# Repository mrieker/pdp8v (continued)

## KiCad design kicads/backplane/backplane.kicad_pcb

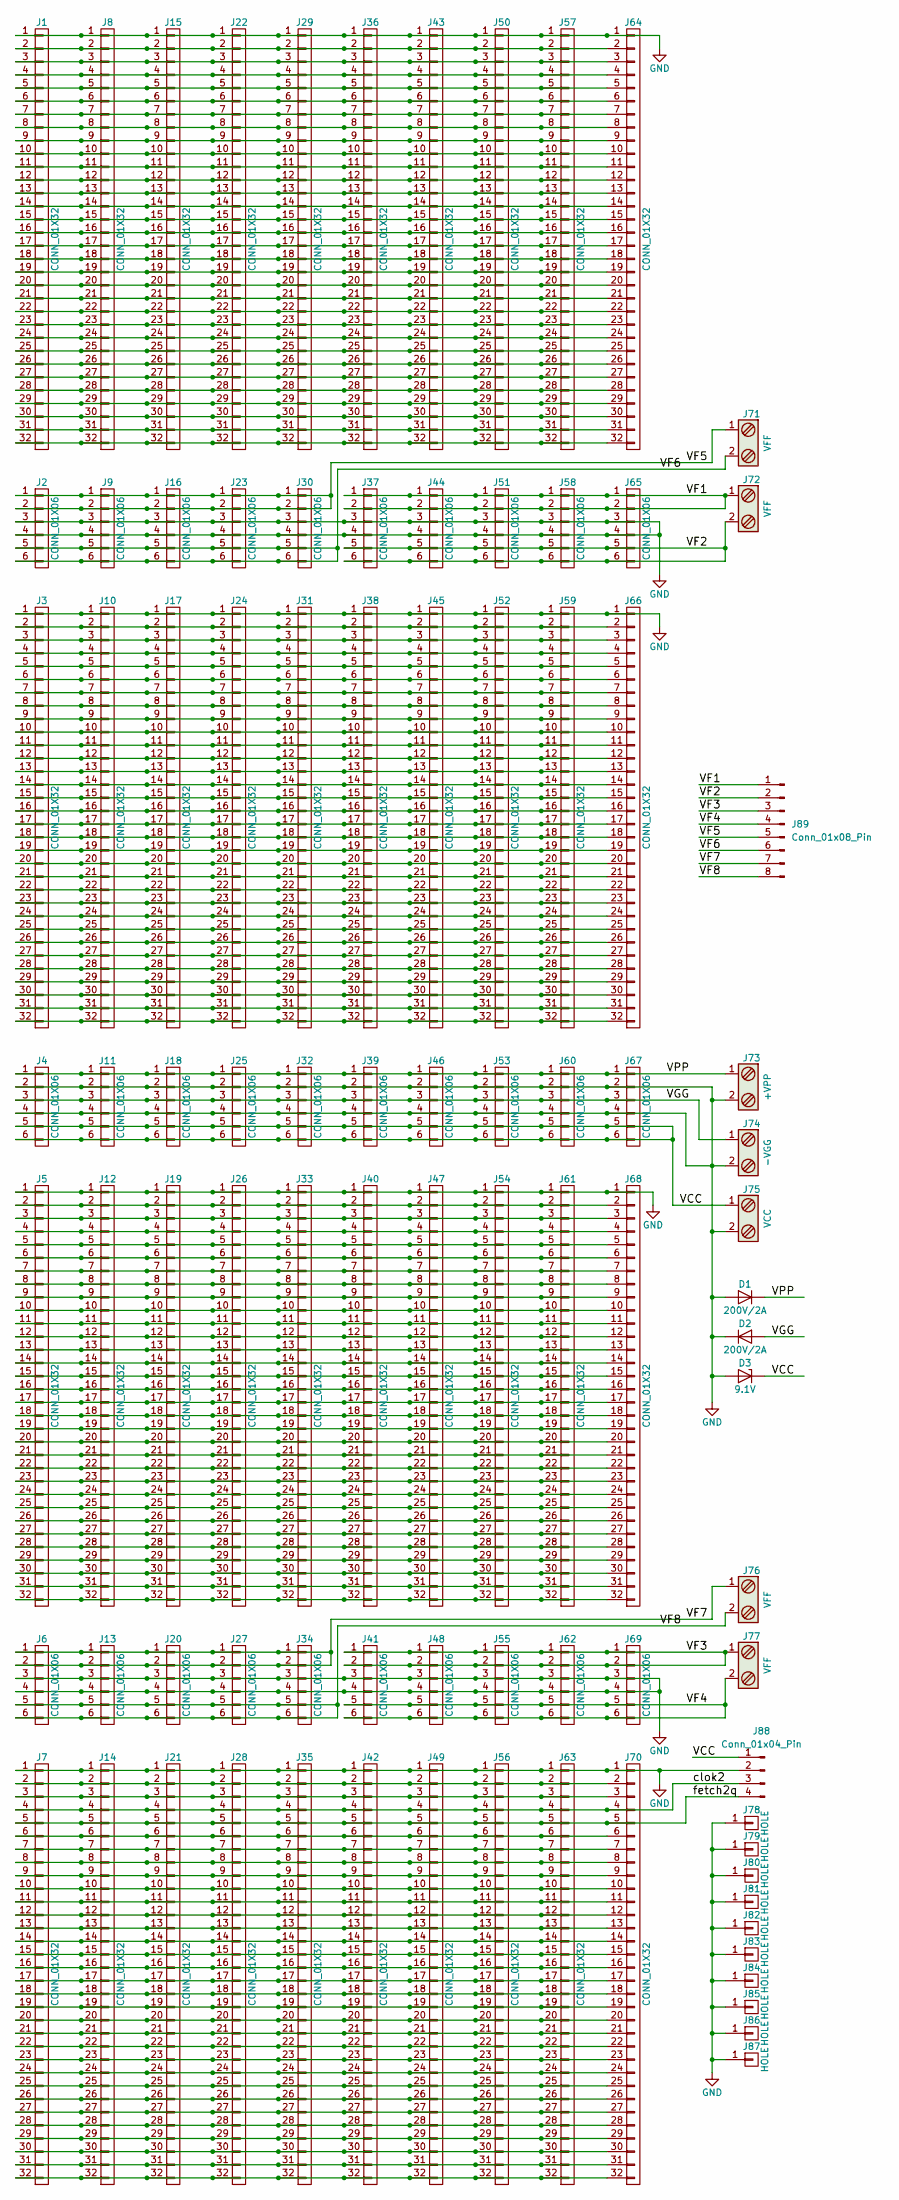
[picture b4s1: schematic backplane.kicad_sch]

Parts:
D1, D2: 200V/2A; D_DO-15_P12.70mm_Horizontal
D3: 9.1V; D_DO-15_P12.70mm_Horizontal
J1, J3, J5, J7, J8, J10, J12, J14, J15, J17, J19, J21, J22, J24, J26, J28, J29, J31, J33, J35, J36, J38, J40, J42, J43, J45, J47, J49, J50, J52, J54, J56, J57, J59, J61, J63, J64, J66, J68, J70: CONN_01X32; Pin_Header_Straight_1x32_Pitch2.54mm
J2, J4, J6, J9, J11, J13, J16, J18, J20, J23, J25, J27, J30, J32, J34, J37, J39, J41, J44, J46, J48, J51, J53, J55, J58, J60, J62, J65, J67, J69: CONN_01X06; Pin_Header_Straight_1x06_Pitch2.54mm
J71, J72, J76, J77: VFF; WireConnection_2.50mmDrill_LargePad
J73: +VPP; WireConnection_2.50mmDrill_LargePad
J74: -VGG; WireConnection_2.50mmDrill_LargePad
J75: VCC; WireConnection_2.50mmDrill_LargePad
J78, J79, J80, J81, J82, J83, J84, J85, J86, J87: HOLE; 1pin
J88: Conn_01x04_Pin; PinHeader_1x04_P2.54mm_Vertical
J89: Conn_01x08_Pin; PinHeader_1x08_P2.54mm_Vertical

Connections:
/VCC: D3.1 (K), J4.5, J4.6, J11.5, J11.6, J18.5, J18.6, J25.5, J25.6, J32.5, J32.6, J39.5, J39.6, J46.5, J46.6, J53.5, J53.6, J60.5, J60.6, J67.5, J67.6, J75.1, J88.1
/VF1: J37.1, J37.2, J44.1, J44.2, J51.1, J51.2, J58.1, J58.2, J65.1, J65.2, J72.1, J89.1
/VF2: J37.5, J37.6, J44.5, J44.6, J51.5, J51.6, J58.5, J58.6, J65.5, J65.6, J72.2, J89.2
/VF3: J41.1, J41.2, J48.1, J48.2, J55.1, J55.2, J62.1, J62.2, J69.1, J69.2, J77.1, J89.3
/VF4: J41.5, J41.6, J48.5, J48.6, J55.5, J55.6, J62.5, J62.6, J69.5, J69.6, J77.2, J89.4
/VF5: J2.1, J2.2, J9.1, J9.2, J16.1, J16.2, J23.1, J23.2, J30.1, J30.2, J71.1, J89.5
/VF6: J2.5, J2.6, J9.5, J9.6, J16.5, J16.6, J23.5, J23.6, J30.5, J30.6, J71.2, J89.6
/VF7: J6.1, J6.2, J13.1, J13.2, J20.1, J20.2, J27.1, J27.2, J34.1, J34.2, J76.1, J89.7
/VF8: J6.5, J6.6, J13.5, J13.6, J20.5, J20.6, J27.5, J27.6, J34.5, J34.6, J76.2, J89.8
/VGG: D2.2 (A), J4.3, J11.3, J18.3, J25.3, J32.3, J39.3, J46.3, J53.3, J60.3, J67.3, J74.1
/VPP: D1.1 (K), J4.1, J11.1, J18.1, J25.1, J32.1, J39.1, J46.1, J53.1, J60.1, J67.1, J73.1
/clok2: J7.4, J14.4, J21.4, J28.4, J35.4, J42.4, J49.4, J56.4, J63.4, J70.4, J88.3
/fetch2q: J7.5, J14.5, J21.5, J28.5, J35.5, J42.5, J49.5, J56.5, J63.5, J70.5, J88.4
GND: D1.2 (A), D2.1 (K), D3.2 (A), J1.1, J2.3, J2.4, J3.1, J4.2, J4.4, J5.1, J6.3, J6.4, J7.1, J8.1, J9.3, J9.4, J10.1, J11.2, J11.4, J12.1, J13.3, J13.4, J14.1, J15.1, J16.3, J16.4, J17.1, J18.2, J18.4, J19.1, J20.3, J20.4, J21.1, J22.1, J23.3, J23.4, J24.1, J25.2, J25.4, J26.1, J27.3, J27.4, J28.1, J29.1, J30.3, J30.4, J31.1, J32.2, J32.4, J33.1, J34.3, J34.4, J35.1, J36.1, J37.3, J37.4, J38.1, J39.2, J39.4, J40.1, J41.3, J41.4, J42.1, J43.1, J44.3, J44.4, J45.1, J46.2, J46.4, J47.1, J48.3, J48.4, J49.1, J50.1, J51.3, J51.4, J52.1, J53.2, J53.4, J54.1, J55.3, J55.4, J56.1, J57.1, J58.3, J58.4, J59.1, J60.2, J60.4, J61.1, J62.3, J62.4, J63.1, J64.1, J65.3, J65.4, J66.1, J67.2, J67.4, J68.1, J69.3, J69.4, J70.1, J73.2, J74.2, J75.2, J78.1, J79.1, J80.1, J81.1, J82.1, J83.1, J84.1, J85.1, J86.1, J87.1, J88.2
unnamed: J1.2, J8.2, J15.2, J22.2, J29.2, J36.2, J43.2, J50.2, J57.2, J64.2
unnamed: J1.3, J8.3, J15.3, J22.3, J29.3, J36.3, J43.3, J50.3, J57.3, J64.3
unnamed: J1.4, J8.4, J15.4, J22.4, J29.4, J36.4, J43.4, J50.4, J57.4, J64.4
unnamed: J1.5, J8.5, J15.5, J22.5, J29.5, J36.5, J43.5, J50.5, J57.5, J64.5
unnamed: J1.6, J8.6, J15.6, J22.6, J29.6, J36.6, J43.6, J50.6, J57.6, J64.6
unnamed: J1.7, J8.7, J15.7, J22.7, J29.7, J36.7, J43.7, J50.7, J57.7, J64.7
unnamed: J1.8, J8.8, J15.8, J22.8, J29.8, J36.8, J43.8, J50.8, J57.8, J64.8
unnamed: J1.9, J8.9, J15.9, J22.9, J29.9, J36.9, J43.9, J50.9, J57.9, J64.9
unnamed: J1.10, J8.10, J15.10, J22.10, J29.10, J36.10, J43.10, J50.10, J57.10, J64.10
unnamed: J1.11, J8.11, J15.11, J22.11, J29.11, J36.11, J43.11, J50.11, J57.11, J64.11
unnamed: J1.12, J8.12, J15.12, J22.12, J29.12, J36.12, J43.12, J50.12, J57.12, J64.12
unnamed: J1.13, J8.13, J15.13, J22.13, J29.13, J36.13, J43.13, J50.13, J57.13, J64.13
unnamed: J1.14, J8.14, J15.14, J22.14, J29.14, J36.14, J43.14, J50.14, J57.14, J64.14
unnamed: J1.15, J8.15, J15.15, J22.15, J29.15, J36.15, J43.15, J50.15, J57.15, J64.15
unnamed: J1.16, J8.16, J15.16, J22.16, J29.16, J36.16, J43.16, J50.16, J57.16, J64.16
unnamed: J1.17, J8.17, J15.17, J22.17, J29.17, J36.17, J43.17, J50.17, J57.17, J64.17
unnamed: J1.18, J8.18, J15.18, J22.18, J29.18, J36.18, J43.18, J50.18, J57.18, J64.18
unnamed: J1.19, J8.19, J15.19, J22.19, J29.19, J36.19, J43.19, J50.19, J57.19, J64.19
unnamed: J1.20, J8.20, J15.20, J22.20, J29.20, J36.20, J43.20, J50.20, J57.20, J64.20
unnamed: J1.21, J8.21, J15.21, J22.21, J29.21, J36.21, J43.21, J50.21, J57.21, J64.21
unnamed: J1.22, J8.22, J15.22, J22.22, J29.22, J36.22, J43.22, J50.22, J57.22, J64.22
unnamed: J1.23, J8.23, J15.23, J22.23, J29.23, J36.23, J43.23, J50.23, J57.23, J64.23
unnamed: J1.24, J8.24, J15.24, J22.24, J29.24, J36.24, J43.24, J50.24, J57.24, J64.24
unnamed: J1.25, J8.25, J15.25, J22.25, J29.25, J36.25, J43.25, J50.25, J57.25, J64.25
unnamed: J1.26, J8.26, J15.26, J22.26, J29.26, J36.26, J43.26, J50.26, J57.26, J64.26
unnamed: J1.27, J8.27, J15.27, J22.27, J29.27, J36.27, J43.27, J50.27, J57.27, J64.27
unnamed: J1.28, J8.28, J15.28, J22.28, J29.28, J36.28, J43.28, J50.28, J57.28, J64.28
unnamed: J1.29, J8.29, J15.29, J22.29, J29.29, J36.29, J43.29, J50.29, J57.29, J64.29
unnamed: J1.30, J8.30, J15.30, J22.30, J29.30, J36.30, J43.30, J50.30, J57.30, J64.30
unnamed: J1.31, J8.31, J15.31, J22.31, J29.31, J36.31, J43.31, J50.31, J57.31, J64.31
unnamed: J1.32, J8.32, J15.32, J22.32, J29.32, J36.32, J43.32, J50.32, J57.32, J64.32
unnamed: J3.2, J10.2, J17.2, J24.2, J31.2, J38.2, J45.2, J52.2, J59.2, J66.2
unnamed: J3.3, J10.3, J17.3, J24.3, J31.3, J38.3, J45.3, J52.3, J59.3, J66.3
unnamed: J3.4, J10.4, J17.4, J24.4, J31.4, J38.4, J45.4, J52.4, J59.4, J66.4
unnamed: J3.5, J10.5, J17.5, J24.5, J31.5, J38.5, J45.5, J52.5, J59.5, J66.5
unnamed: J3.6, J10.6, J17.6, J24.6, J31.6, J38.6, J45.6, J52.6, J59.6, J66.6
unnamed: J3.7, J10.7, J17.7, J24.7, J31.7, J38.7, J45.7, J52.7, J59.7, J66.7
unnamed: J3.8, J10.8, J17.8, J24.8, J31.8, J38.8, J45.8, J52.8, J59.8, J66.8
unnamed: J3.9, J10.9, J17.9, J24.9, J31.9, J38.9, J45.9, J52.9, J59.9, J66.9
unnamed: J3.10, J10.10, J17.10, J24.10, J31.10, J38.10, J45.10, J52.10, J59.10, J66.10
unnamed: J3.11, J10.11, J17.11, J24.11, J31.11, J38.11, J45.11, J52.11, J59.11, J66.11
unnamed: J3.12, J10.12, J17.12, J24.12, J31.12, J38.12, J45.12, J52.12, J59.12, J66.12
unnamed: J3.13, J10.13, J17.13, J24.13, J31.13, J38.13, J45.13, J52.13, J59.13, J66.13
unnamed: J3.14, J10.14, J17.14, J24.14, J31.14, J38.14, J45.14, J52.14, J59.14, J66.14
unnamed: J3.15, J10.15, J17.15, J24.15, J31.15, J38.15, J45.15, J52.15, J59.15, J66.15
unnamed: J3.16, J10.16, J17.16, J24.16, J31.16, J38.16, J45.16, J52.16, J59.16, J66.16
unnamed: J3.17, J10.17, J17.17, J24.17, J31.17, J38.17, J45.17, J52.17, J59.17, J66.17
unnamed: J3.18, J10.18, J17.18, J24.18, J31.18, J38.18, J45.18, J52.18, J59.18, J66.18
unnamed: J3.19, J10.19, J17.19, J24.19, J31.19, J38.19, J45.19, J52.19, J59.19, J66.19
unnamed: J3.20, J10.20, J17.20, J24.20, J31.20, J38.20, J45.20, J52.20, J59.20, J66.20
unnamed: J3.21, J10.21, J17.21, J24.21, J31.21, J38.21, J45.21, J52.21, J59.21, J66.21
unnamed: J3.22, J10.22, J17.22, J24.22, J31.22, J38.22, J45.22, J52.22, J59.22, J66.22
unnamed: J3.23, J10.23, J17.23, J24.23, J31.23, J38.23, J45.23, J52.23, J59.23, J66.23
unnamed: J3.24, J10.24, J17.24, J24.24, J31.24, J38.24, J45.24, J52.24, J59.24, J66.24
unnamed: J3.25, J10.25, J17.25, J24.25, J31.25, J38.25, J45.25, J52.25, J59.25, J66.25
unnamed: J3.26, J10.26, J17.26, J24.26, J31.26, J38.26, J45.26, J52.26, J59.26, J66.26
unnamed: J3.27, J10.27, J17.27, J24.27, J31.27, J38.27, J45.27, J52.27, J59.27, J66.27
unnamed: J3.28, J10.28, J17.28, J24.28, J31.28, J38.28, J45.28, J52.28, J59.28, J66.28
unnamed: J3.29, J10.29, J17.29, J24.29, J31.29, J38.29, J45.29, J52.29, J59.29, J66.29
unnamed: J3.30, J10.30, J17.30, J24.30, J31.30, J38.30, J45.30, J52.30, J59.30, J66.30
unnamed: J3.31, J10.31, J17.31, J24.31, J31.31, J38.31, J45.31, J52.31, J59.31, J66.31
unnamed: J3.32, J10.32, J17.32, J24.32, J31.32, J38.32, J45.32, J52.32, J59.32, J66.32
unnamed: J5.2, J12.2, J19.2, J26.2, J33.2, J40.2, J47.2, J54.2, J61.2, J68.2
unnamed: J5.3, J12.3, J19.3, J26.3, J33.3, J40.3, J47.3, J54.3, J61.3, J68.3
unnamed: J5.4, J12.4, J19.4, J26.4, J33.4, J40.4, J47.4, J54.4, J61.4, J68.4
unnamed: J5.5, J12.5, J19.5, J26.5, J33.5, J40.5, J47.5, J54.5, J61.5, J68.5
unnamed: J5.6, J12.6, J19.6, J26.6, J33.6, J40.6, J47.6, J54.6, J61.6, J68.6
unnamed: J5.7, J12.7, J19.7, J26.7, J33.7, J40.7, J47.7, J54.7, J61.7, J68.7
unnamed: J5.8, J12.8, J19.8, J26.8, J33.8, J40.8, J47.8, J54.8, J61.8, J68.8
unnamed: J5.9, J12.9, J19.9, J26.9, J33.9, J40.9, J47.9, J54.9, J61.9, J68.9
unnamed: J5.10, J12.10, J19.10, J26.10, J33.10, J40.10, J47.10, J54.10, J61.10, J68.10
unnamed: J5.11, J12.11, J19.11, J26.11, J33.11, J40.11, J47.11, J54.11, J61.11, J68.11
unnamed: J5.12, J12.12, J19.12, J26.12, J33.12, J40.12, J47.12, J54.12, J61.12, J68.12
unnamed: J5.13, J12.13, J19.13, J26.13, J33.13, J40.13, J47.13, J54.13, J61.13, J68.13
unnamed: J5.14, J12.14, J19.14, J26.14, J33.14, J40.14, J47.14, J54.14, J61.14, J68.14
unnamed: J5.15, J12.15, J19.15, J26.15, J33.15, J40.15, J47.15, J54.15, J61.15, J68.15
unnamed: J5.16, J12.16, J19.16, J26.16, J33.16, J40.16, J47.16, J54.16, J61.16, J68.16
unnamed: J5.17, J12.17, J19.17, J26.17, J33.17, J40.17, J47.17, J54.17, J61.17, J68.17
unnamed: J5.18, J12.18, J19.18, J26.18, J33.18, J40.18, J47.18, J54.18, J61.18, J68.18
unnamed: J5.19, J12.19, J19.19, J26.19, J33.19, J40.19, J47.19, J54.19, J61.19, J68.19
unnamed: J5.20, J12.20, J19.20, J26.20, J33.20, J40.20, J47.20, J54.20, J61.20, J68.20
unnamed: J5.21, J12.21, J19.21, J26.21, J33.21, J40.21, J47.21, J54.21, J61.21, J68.21
unnamed: J5.22, J12.22, J19.22, J26.22, J33.22, J40.22, J47.22, J54.22, J61.22, J68.22
unnamed: J5.23, J12.23, J19.23, J26.23, J33.23, J40.23, J47.23, J54.23, J61.23, J68.23
unnamed: J5.24, J12.24, J19.24, J26.24, J33.24, J40.24, J47.24, J54.24, J61.24, J68.24
unnamed: J5.25, J12.25, J19.25, J26.25, J33.25, J40.25, J47.25, J54.25, J61.25, J68.25
unnamed: J5.26, J12.26, J19.26, J26.26, J33.26, J40.26, J47.26, J54.26, J61.26, J68.26
unnamed: J5.27, J12.27, J19.27, J26.27, J33.27, J40.27, J47.27, J54.27, J61.27, J68.27
unnamed: J5.28, J12.28, J19.28, J26.28, J33.28, J40.28, J47.28, J54.28, J61.28, J68.28
unnamed: J5.29, J12.29, J19.29, J26.29, J33.29, J40.29, J47.29, J54.29, J61.29, J68.29
unnamed: J5.30, J12.30, J19.30, J26.30, J33.30, J40.30, J47.30, J54.30, J61.30, J68.30
unnamed: J5.31, J12.31, J19.31, J26.31, J33.31, J40.31, J47.31, J54.31, J61.31, J68.31
unnamed: J5.32, J12.32, J19.32, J26.32, J33.32, J40.32, J47.32, J54.32, J61.32, J68.32
unnamed: J7.2, J14.2, J21.2, J28.2, J35.2, J42.2, J49.2, J56.2, J63.2, J70.2
unnamed: J7.3, J14.3, J21.3, J28.3, J35.3, J42.3, J49.3, J56.3, J63.3, J70.3
unnamed: J7.6, J14.6, J21.6, J28.6, J35.6, J42.6, J49.6, J56.6, J63.6, J70.6
unnamed: J7.7, J14.7, J21.7, J28.7, J35.7, J42.7, J49.7, J56.7, J63.7, J70.7
unnamed: J7.8, J14.8, J21.8, J28.8, J35.8, J42.8, J49.8, J56.8, J63.8, J70.8
unnamed: J7.9, J14.9, J21.9, J28.9, J35.9, J42.9, J49.9, J56.9, J63.9, J70.9
unnamed: J7.10, J14.10, J21.10, J28.10, J35.10, J42.10, J49.10, J56.10, J63.10, J70.10
unnamed: J7.11, J14.11, J21.11, J28.11, J35.11, J42.11, J49.11, J56.11, J63.11, J70.11
unnamed: J7.12, J14.12, J21.12, J28.12, J35.12, J42.12, J49.12, J56.12, J63.12, J70.12
unnamed: J7.13, J14.13, J21.13, J28.13, J35.13, J42.13, J49.13, J56.13, J63.13, J70.13
unnamed: J7.14, J14.14, J21.14, J28.14, J35.14, J42.14, J49.14, J56.14, J63.14, J70.14
unnamed: J7.15, J14.15, J21.15, J28.15, J35.15, J42.15, J49.15, J56.15, J63.15, J70.15
unnamed: J7.16, J14.16, J21.16, J28.16, J35.16, J42.16, J49.16, J56.16, J63.16, J70.16
unnamed: J7.17, J14.17, J21.17, J28.17, J35.17, J42.17, J49.17, J56.17, J63.17, J70.17
unnamed: J7.18, J14.18, J21.18, J28.18, J35.18, J42.18, J49.18, J56.18, J63.18, J70.18
unnamed: J7.19, J14.19, J21.19, J28.19, J35.19, J42.19, J49.19, J56.19, J63.19, J70.19
unnamed: J7.20, J14.20, J21.20, J28.20, J35.20, J42.20, J49.20, J56.20, J63.20, J70.20
unnamed: J7.21, J14.21, J21.21, J28.21, J35.21, J42.21, J49.21, J56.21, J63.21, J70.21
unnamed: J7.22, J14.22, J21.22, J28.22, J35.22, J42.22, J49.22, J56.22, J63.22, J70.22
unnamed: J7.23, J14.23, J21.23, J28.23, J35.23, J42.23, J49.23, J56.23, J63.23, J70.23
unnamed: J7.24, J14.24, J21.24, J28.24, J35.24, J42.24, J49.24, J56.24, J63.24, J70.24
unnamed: J7.25, J14.25, J21.25, J28.25, J35.25, J42.25, J49.25, J56.25, J63.25, J70.25
unnamed: J7.26, J14.26, J21.26, J28.26, J35.26, J42.26, J49.26, J56.26, J63.26, J70.26
unnamed: J7.27, J14.27, J21.27, J28.27, J35.27, J42.27, J49.27, J56.27, J63.27, J70.27
unnamed: J7.28, J14.28, J21.28, J28.28, J35.28, J42.28, J49.28, J56.28, J63.28, J70.28
unnamed: J7.29, J14.29, J21.29, J28.29, J35.29, J42.29, J49.29, J56.29, J63.29, J70.29
unnamed: J7.30, J14.30, J21.30, J28.30, J35.30, J42.30, J49.30, J56.30, J63.30, J70.30
unnamed: J7.31, J14.31, J21.31, J28.31, J35.31, J42.31, J49.31, J56.31, J63.31, J70.31
unnamed: J7.32, J14.32, J21.32, J28.32, J35.32, J42.32, J49.32, J56.32, J63.32, J70.32

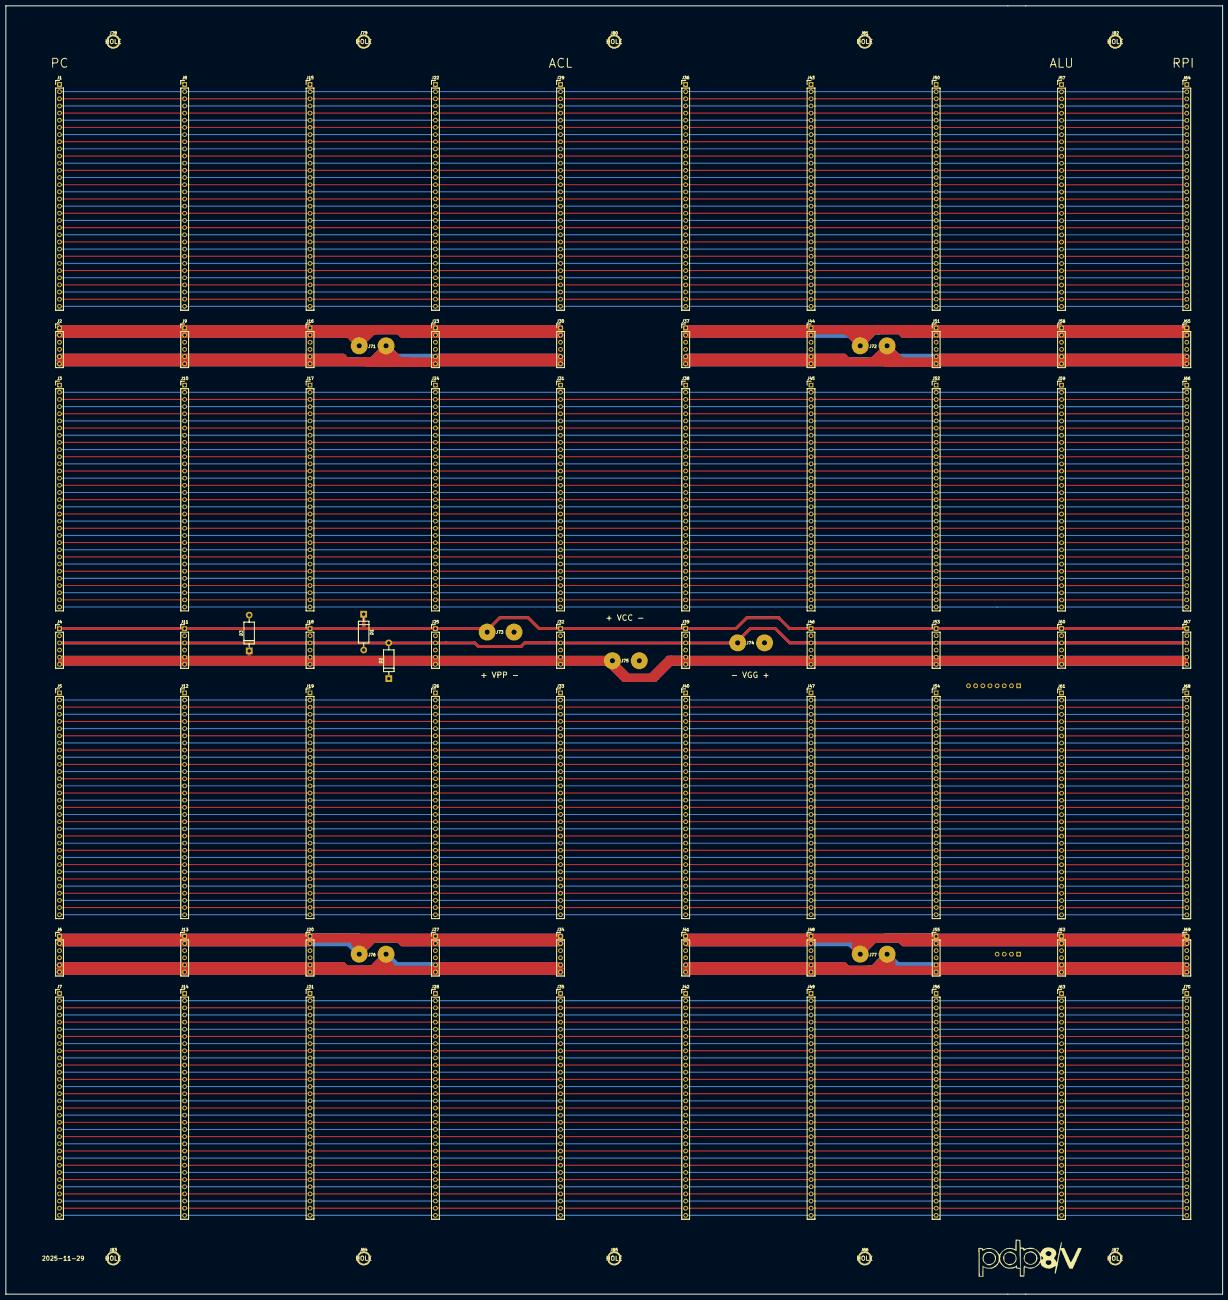
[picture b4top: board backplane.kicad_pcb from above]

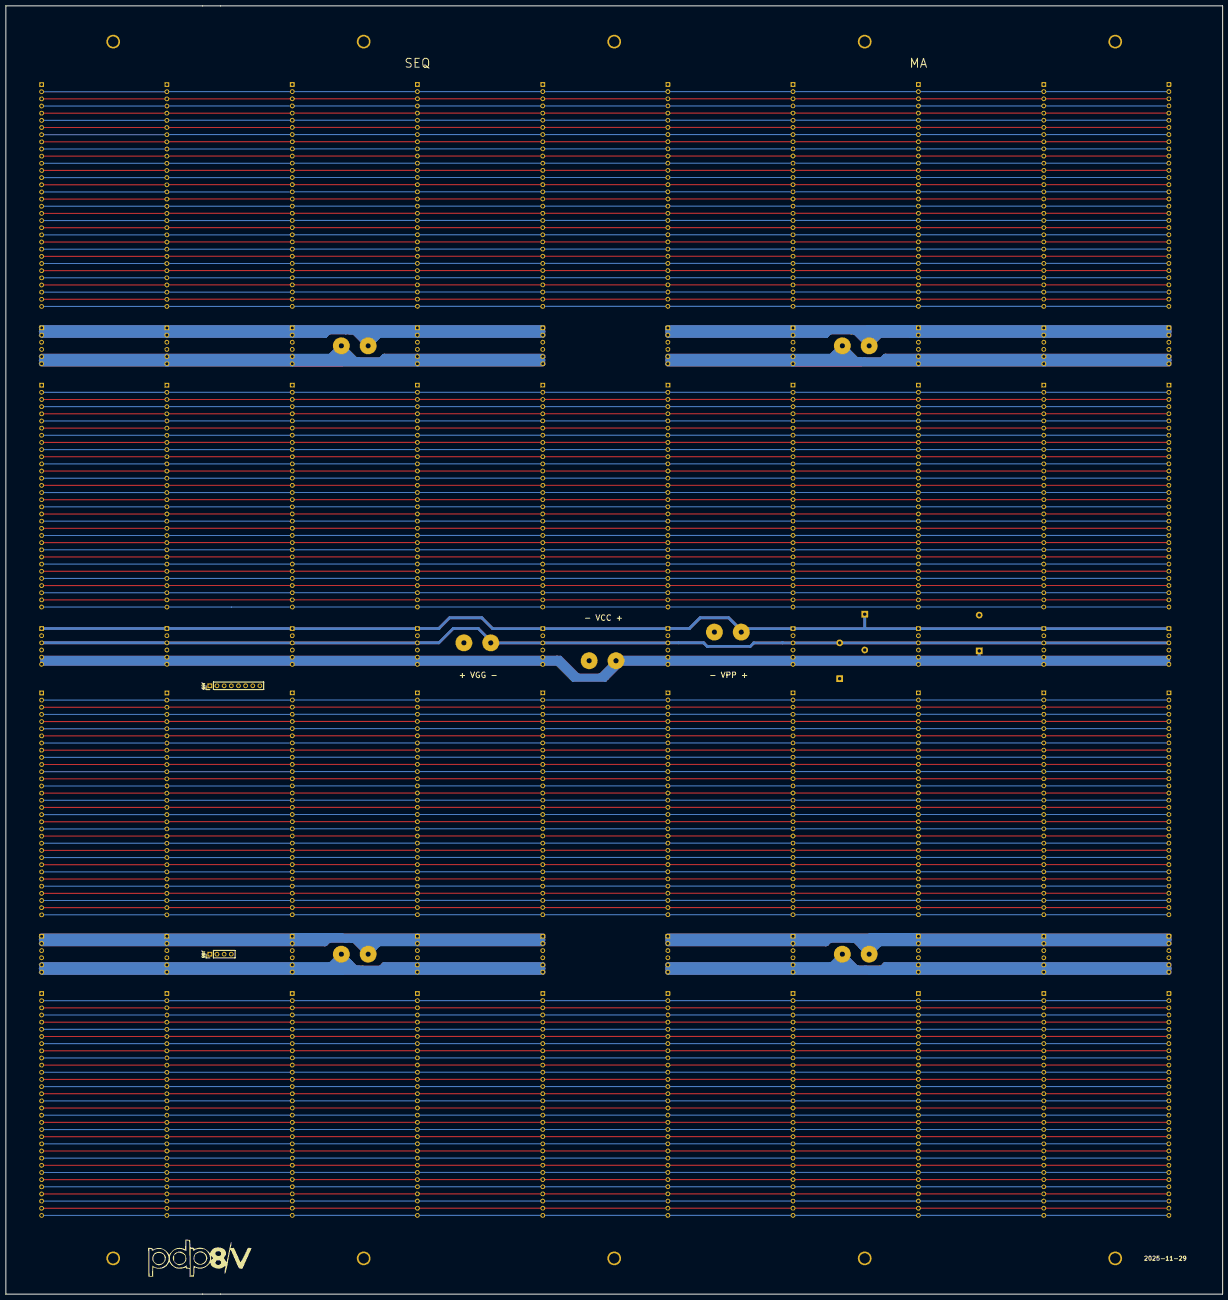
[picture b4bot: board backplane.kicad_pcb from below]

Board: 4 copper layers, 431.8 x 457.2 mm, 92 parts (2 on the bottom side), 136 nets.

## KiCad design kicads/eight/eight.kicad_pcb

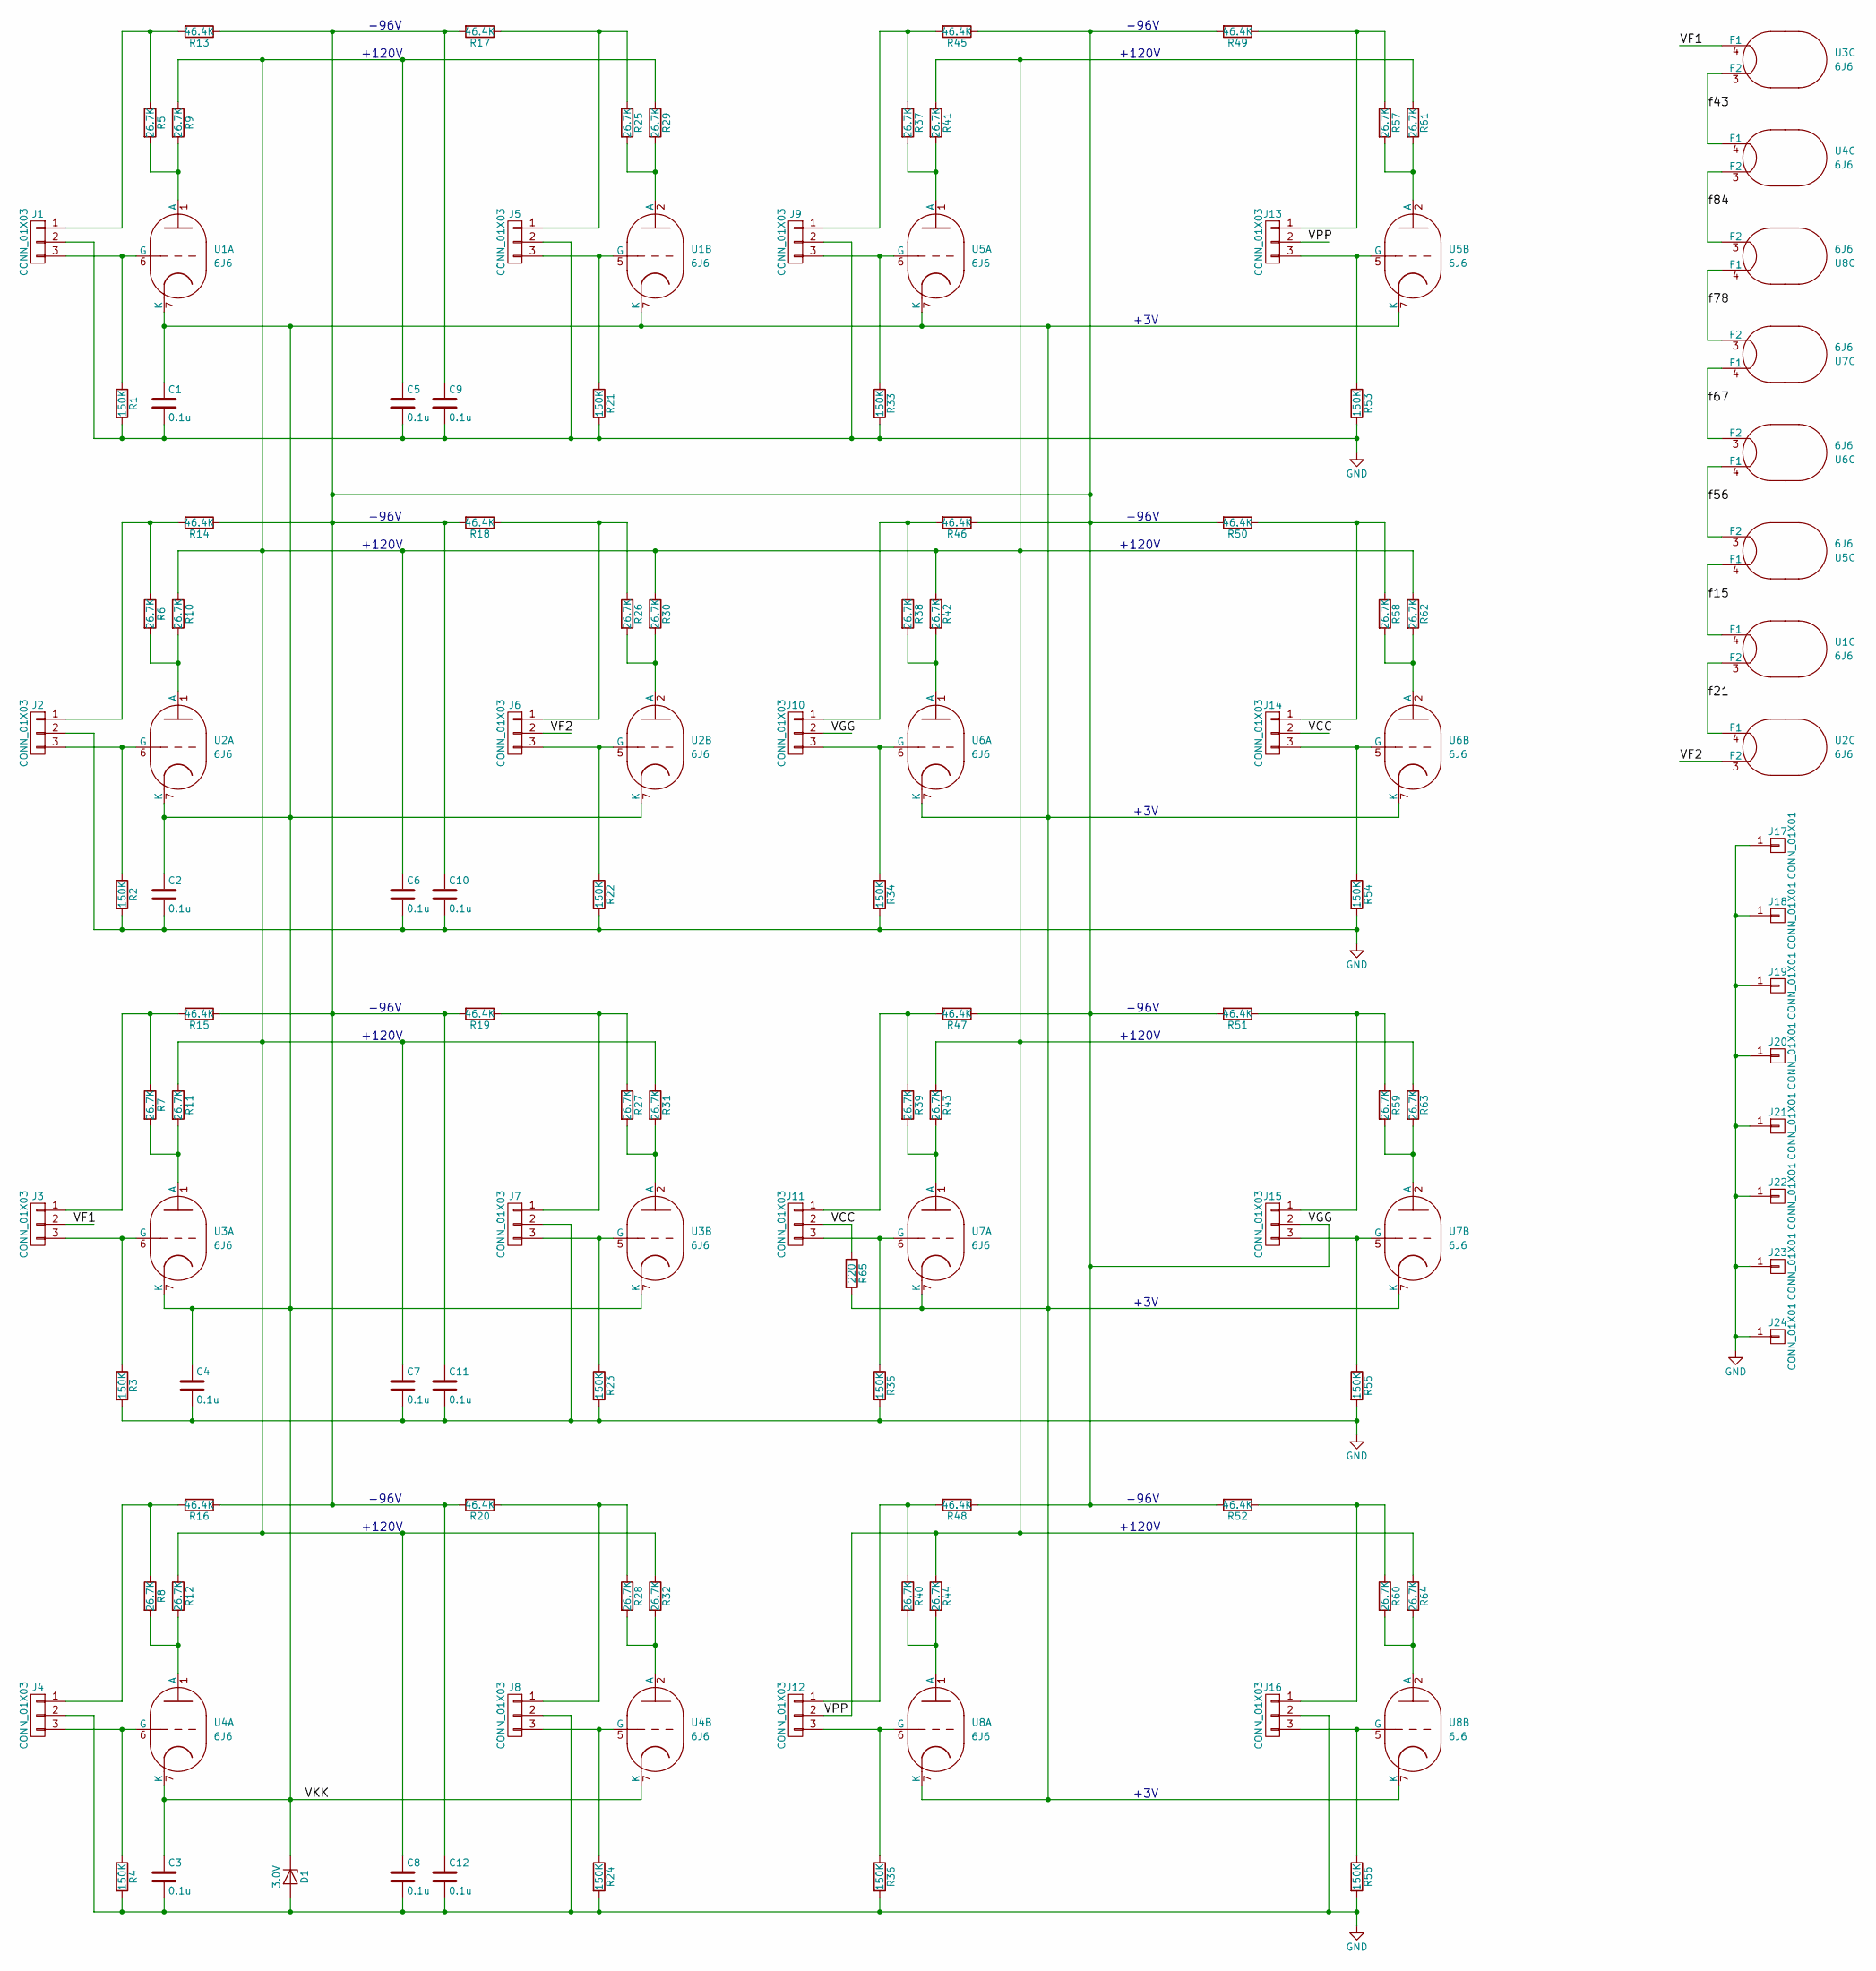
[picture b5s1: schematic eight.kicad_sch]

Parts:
C1, C2, C3, C4, C5, C6, C7, C8, C9, C10, C11, C12: 0.1u; C_Axial_0.1uF
D1: 3.0V; D_DO-35_SOD27_P7.62mm_Horizontal
J1, J2, J3, J4, J5, J6, J7, J8, J9, J10, J11, J12, J13, J14, J15, J16: CONN_01X03; Pin_Header_Straight_1x03_Pitch2.54mm
J17, J18, J19, J20, J21, J22, J23, J24: CONN_01X01; Pin_Header_Straight_1x01_Pitch2.54mm
R1, R2, R3, R4, R21, R22, R23, R24, R33, R34, R35, R36, R53, R54, R55, R56: 150K; R_Axial_QtrWatt
R5, R6, R7, R8, R9, R10, R11, R12, R25, R26, R27, R28, R29, R30, R31, R32, R37, R38, R39, R40, R41, R42, R43, R44, R57, R58, R59, R60, R61, R62, R63, R64: 26.7K; R_Axial_QtrWatt
R13, R14, R15, R16, R17, R18, R19, R20, R45, R46, R47, R48, R49, R50, R51, R52: 46.4K; R_Axial_QtrWatt
R65: 220; R_Axial_QtrWatt
U1, U2, U3, U4, U5, U6, U7, U8: 6J6; B7G-0.7dia

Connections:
/VCC: J11.2, J14.2, R65.1
/VF1: J3.2, U3.4 (F1)
/VF2: J6.2, U2.3 (F2)
/VGG: C9.1, C10.1, C11.1, C12.1, J10.2, J15.2, R13.1, R14.1, R15.1, R16.1, R17.2, R18.2, R19.2, R20.2, R45.1, R46.1, R47.1, R48.1, R49.2, R50.2, R51.2, R52.2
/VKK: C1.1, C2.1, C3.1, C4.1, D1.1 (K), R65.2, U1.7 (K), U2.7 (K), U3.7 (K), U4.7 (K), U5.7 (K), U6.7 (K), U7.7 (K), U8.7 (K)
/VPP: C5.1, C6.1, C7.1, C8.1, J12.2, J13.2, R9.1, R10.1, R11.1, R12.1, R29.1, R30.1, R31.1, R32.1, R41.1, R42.1, R43.1, R44.1, R61.1, R62.1, R63.1, R64.1
/f15: U1.4 (F1), U5.4 (F1)
/f21: U1.3 (F2), U2.4 (F1)
/f43: U3.3 (F2), U4.4 (F1)
/f56: U5.3 (F2), U6.4 (F1)
/f67: U6.3 (F2), U7.4 (F1)
/f78: U7.3 (F2), U8.4 (F1)
/f84: U4.3 (F2), U8.3 (F2)
GND: C1.2, C2.2, C3.2, C4.2, C5.2, C6.2, C7.2, C8.2, C9.2, C10.2, C11.2, C12.2, D1.2 (A), J1.2, J2.2, J4.2, J5.2, J7.2, J8.2, J9.2, J16.2, J17.1, J18.1, J19.1, J20.1, J21.1, J22.1, J23.1, J24.1, R1.2, R2.2, R3.2, R4.2, R21.2, R22.2, R23.2, R24.2, R33.2, R34.2, R35.2, R36.2, R53.2, R54.2, R55.2, R56.2
unnamed: J1.1, R5.1, R13.2
unnamed: J1.3, R1.1, U1.6 (G)
unnamed: J2.1, R6.1, R14.2
unnamed: J2.3, R2.1, U2.6 (G)
unnamed: J3.1, R7.1, R15.2
unnamed: J3.3, R3.1, U3.6 (G)
unnamed: J4.1, R8.1, R16.2
unnamed: J4.3, R4.1, U4.6 (G)
unnamed: J5.1, R17.1, R25.1
unnamed: J5.3, R21.1, U1.5 (G)
unnamed: J6.1, R18.1, R26.1
unnamed: J6.3, R22.1, U2.5 (G)
unnamed: J7.1, R19.1, R27.1
unnamed: J7.3, R23.1, U3.5 (G)
unnamed: J8.1, R20.1, R28.1
unnamed: J8.3, R24.1, U4.5 (G)
unnamed: J9.1, R37.1, R45.2
unnamed: J9.3, R33.1, U5.6 (G)
unnamed: J10.1, R38.1, R46.2
unnamed: J10.3, R34.1, U6.6 (G)
unnamed: J11.1, R39.1, R47.2
unnamed: J11.3, R35.1, U7.6 (G)
unnamed: J12.1, R40.1, R48.2
unnamed: J12.3, R36.1, U8.6 (G)
unnamed: J13.1, R49.1, R57.1
unnamed: J13.3, R53.1, U5.5 (G)
unnamed: J14.1, R50.1, R58.1
unnamed: J14.3, R54.1, U6.5 (G)
unnamed: J15.1, R51.1, R59.1
unnamed: J15.3, R55.1, U7.5 (G)
unnamed: J16.1, R52.1, R60.1
unnamed: J16.3, R56.1, U8.5 (G)
unnamed: R5.2, R9.2, U1.1 (A)
unnamed: R25.2, R29.2, U1.2 (A)
unnamed: R6.2, R10.2, U2.1 (A)
unnamed: R26.2, R30.2, U2.2 (A)
unnamed: R7.2, R11.2, U3.1 (A)
unnamed: R27.2, R31.2, U3.2 (A)
unnamed: R8.2, R12.2, U4.1 (A)
unnamed: R28.2, R32.2, U4.2 (A)
unnamed: R37.2, R41.2, U5.1 (A)
unnamed: R57.2, R61.2, U5.2 (A)
unnamed: R38.2, R42.2, U6.1 (A)
unnamed: R58.2, R62.2, U6.2 (A)
unnamed: R39.2, R43.2, U7.1 (A)
unnamed: R59.2, R63.2, U7.2 (A)
unnamed: R40.2, R44.2, U8.1 (A)
unnamed: R60.2, R64.2, U8.2 (A)

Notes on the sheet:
-96V
+3V
+120V

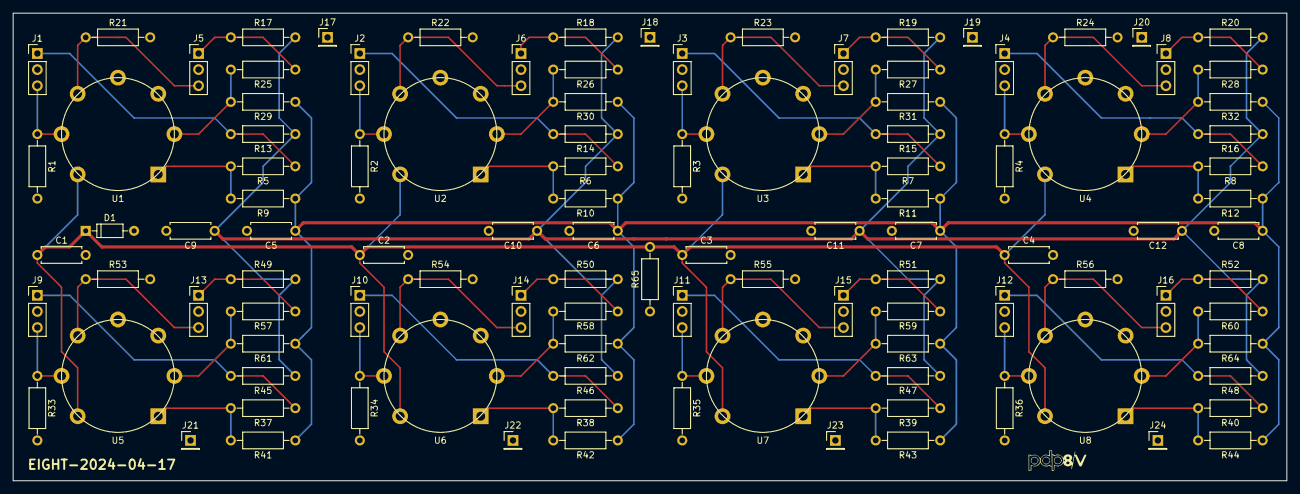
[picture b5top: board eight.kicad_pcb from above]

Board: 4 copper layers, 200.7 x 73.7 mm, 110 parts (0 on the bottom side), 62 nets.
